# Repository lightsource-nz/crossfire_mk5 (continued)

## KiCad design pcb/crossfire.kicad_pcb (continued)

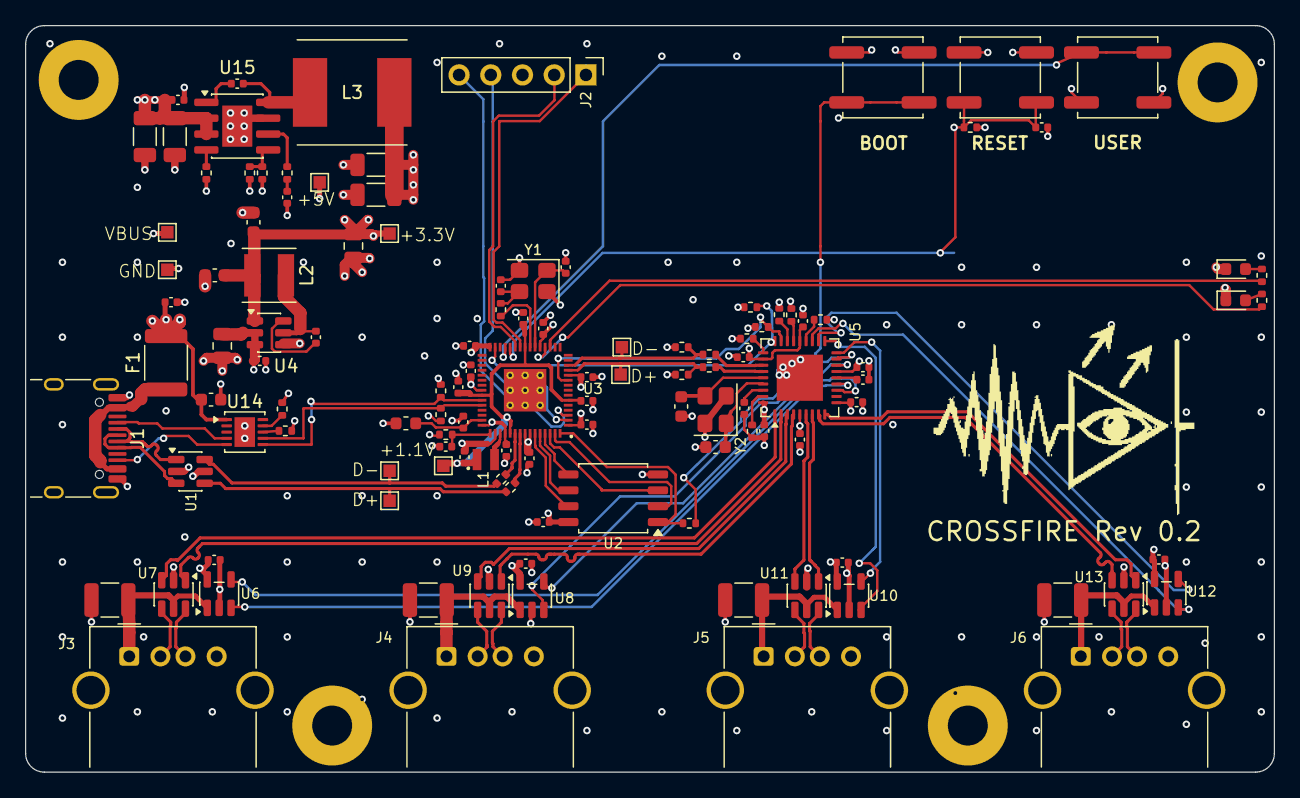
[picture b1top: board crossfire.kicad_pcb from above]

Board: 4 copper layers, 100.0 x 59.8 mm, 124 parts (0 on the bottom side), 92 nets.

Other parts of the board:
G1: crossfire_logo

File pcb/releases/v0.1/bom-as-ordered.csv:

Comment,Designator,Footprint,JLCPCB Part #,Qty,Ext.Price($)
USB-C,J1,USB_C_Receptacle_HRO_TYPE-C-31-M-12_Overhang,C165948,5,0.93
TPS2065C,"U6,U8,U10,U12",SOT-23-5,C353882,22,5.60
RP2350A,U3,rpi_rp2350a_vias,C42411118,5,6.47
330R,"R10,R11",0402,C25104,10,0.01
2.6A,F1,1812,C70127,7,0.43
RESET,"SW1,SW3,SW2",SW_Push_1P1T_NO_CK_KSC6xxJ,C221726,15,9.15
yellow-green,D1,0603,C913102,9,1.06
10k,"R3,R4,R8,R16,R19,R20",0402,C25744,30,0.04
3u3,L1,abracon_aota-b201610s3r3-101-t,C114768,7,0.83
100k,"R12,R24,R25",0402,C25741,15,0.02
4u7,L2,L_4030_Coilcraft_XxL_Sunlord_SWPA,C57269,10,0.66
100R,R9,0402,C25076,5,0.01
12MHz,Y1,Crystal_SMD_3225-4Pin_3.2x2.5mm,C390763,9,0.71
AP63203WU,U4,TSOT-23-6,C780769,5,6.12
W25Q128JVS,U2,SOIC-8,C97521,5,12.90
red,D2,0603,C2286,5,0.04
USBLC6-2SC6,"U1,U7,U9,U11,U13",SOT-23-6,C7519,27,4.85
27R,"R15,R17,R21,R22",0402,C25100,32,0.04
4u7,"C4,C17",0402,C23733,10,0.15
600R,FB1,0603,C85833,20,0.36
10u,"C20,C29",0805,C15850,10,0.43
USB_A,"J3,J4,J5,J6",USB_A_Molex_67643_Horizontal_Overhang,C591765,20,13.71
15p,"C11,C13",0402,C1548,10,0.04
1k,"R7,R23",0402,C11702,10,0.01
100n,"C1,C2,C3,C5,C6,C7,C8,C9,C10,C12,C14,C16,C18,C19,C21,C22,C23,C24,C25,C26,C30,C31,C33,C34,C36,C37,C38,C43,C45",0402,C1525,145,0.51
5k1,"R1,R2",0402,C25905,10,0.02
24MHz,Y2,Crystal_SMD_3225-4Pin_3.2x2.5mm,C70583,9,0.90
12k,R18,0402,C25752,5,0.01
15k,"R13,R14",0402,C25756,10,0.01
22u,"C27,C28",0603,C59461,10,0.31
1u,C15,0402,C29266,25,0.14
18p,"C32,C35",0603,C1647,10,0.12
USB2514B,U5,QFN-36,C16251,5,9.06

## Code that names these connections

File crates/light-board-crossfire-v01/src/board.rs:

//! Board wiring for crossfire revision 0.1: every pin read off the board's own schematic, as
//! recorded in its release specification. Nothing here has been confirmed on hardware yet;
//! the first boards are in production.
//!
//! This lives with the BOARD, not in the port crate or the application: `light-rp2` knows the
//! chip and nothing about what anyone soldered to it, and the application knows neither. This
//! module is the one place that knows which pin carries what, and [`take`] configures every
//! peripheral the board wires up and hands them over once -- the firmware receives owned
//! values, so nothing can reach a peripheral the board did not wire.
//!
//! What the board has, from the processor's side:
//!
//! - the hardware USB pair goes to the USB-C receptacle: the DEVICE role, the console and the
//!   board's entire power supply, and nothing in this module -- the port's shell owns it;
//! - a PIO host pair goes to the hub's upstream port, on [`PIN_HOST_DP`] and [`PIN_HOST_DM`];
//! - the hub is held in reset until the firmware says otherwise, and told when its upstream is
//!   live, on two plain outputs;
//! - two indicators, one button, and the two CC lines of the receptacle on the ADC.
//!
//! The console UART is not constructed here. It is core 1's, built by the firmware's core-1
//! entry on the port's default pair, which is the pair the board wires to the debug header.

use light_core::atomic::{AtomicBool, Ordering};
use light_rp2::adc::Adc;
use light_rp2::gpio::{Input, Output};
use light_rp2::Clocks;

/// The hardware revision this wiring describes, as the board's silkscreen carries it.
pub const REVISION: &str = "0.1";

/// The console, on UART0's default pair, which is also the port's
/// (`light_rp2::shell::UART_TX` / `UART_RX`); brought out on the debug header beside SWD.
pub const PIN_CONSOLE_TX: usize = 0;
pub const PIN_CONSOLE_RX: usize = 1;

/// The hub's active-low reset, with a 10 kΩ pull-down on the board: the hub is held in reset
/// from power-up until this pin is driven high, so a firmware that never touches it has no hub.
pub const PIN_HUB_RESET_N: usize = 7;

/// The PIO USB host pair to the hub's upstream port, 27 Ω in series and 15 kΩ to ground on
/// each line -- the host's pull-downs, so the hub's attach pull-up is seen against them. D+ is
/// the base and D- the next pin up, because the PIO program addresses the pair as a base and
/// an offset.
pub const PIN_HOST_DP: usize = 8;
pub const PIN_HOST_DM: usize = 9;

/// The two indicators, anode to the pin through 330 Ω and cathode to ground: driven high to
/// light, about 4 mA each. The schematic names them LED_1 and LED_2; here they are named by
/// what they look like, since that is what a firmware chooses between.
pub const PIN_LED_RED: usize = 14;
pub const PIN_LED_GREEN: usize = 15;

/// The USER button, to ground, with no pull-up on the board: the pin's own pull-up is what
/// makes it readable, and pressed is low. The other two buttons are not GPIO -- BOOT pulls the
/// flash's chip select and RESET pulls RUN -- so BOOT is read through the port's flash-safe
/// `light_rp2::shell::bootsel`, never as a pin.
pub const PIN_BUTTON: usize = 16;

/// The hub's VBUS_DET input, with a 100 kΩ pull-down on the board: driven high to tell the hub
/// its upstream is live, which is what lets it attach; taken low and high again to make it
/// re-enumerate.
pub const PIN_HUB_VBUS_DET: usize = 18;

/// The receptacle's two CC lines, each terminated with [`CC_RD_OHMS`] to ground at the
/// connector and read here through 10 kΩ and 100 nF: ADC channels 0 and 1. The source's
/// pull-up on whichever line its cable orients to sets the voltage, and that voltage is what
/// the source advertises it can supply.
pub const PIN_CC1_SENSE: usize = 26;
pub const PIN_CC2_SENSE: usize = 27;
/// The termination the board presents on each CC line: the sink's Rd.
pub const CC_RD_OHMS: u32 = 5_100;
/// The ADC's full scale, in millivolts: its reference is the 3.3 V pad supply, through the
/// board's filtered analogue rail.
pub const ADC_FULL_SCALE_MV: u32 = 3_300;

/// The system clock the board is designed for: twenty times its 12 MHz crystal, which gives
/// the PIO host twenty cycles a bit and the flash its fastest legal clock through the divider
/// of 2. The SDK's default is 150 MHz; the firmware's build chooses whether to ask for this.
pub const DESIGN_SYS_HZ: u32 = 240_000_000;

pub struct Peripherals {
        /// Off until lit.
        pub led_red: Output,
        pub led_green: Output,
        /// Pulled up; pressed is low.
        pub button: Input,
        /// Low: the hub is held in reset, as the board's pull-down leaves it from power-up.
        pub hub_reset_n: Output,
        /// Low: the hub has not been told its upstream is live.
        pub hub_vbus_det: Output,
        /// One-shot reads, 12 bits over [`ADC_FULL_SCALE_MV`].
        pub cc1: Adc,
        pub cc2: Adc,
}

static TAKEN: AtomicBool = AtomicBool::new(false);

/// Configure and hand over the board's peripherals. Once.
///
/// Nothing wired today needs a clock rate; the host pair's PIO will, and takes it from here.
pub fn take(clocks: &Clocks) -> Option<Peripherals> {
        if TAKEN.swap(true, Ordering::AcqRel) {
                return None;
        }
        let _ = clocks;
        //   the hub stays exactly where the board's pull-downs put it at power-up -- in reset,
        // with no upstream -- until a firmware decides otherwise: an output constructed low
        // changes nothing on the wire
        Some(Peripherals {
                led_red: Output::new(PIN_LED_RED, false),
                led_green: Output::new(PIN_LED_GREEN, false),
                button: Input::new_pull_up(PIN_BUTTON),
                hub_reset_n: Output::new(PIN_HUB_RESET_N, false),
                hub_vbus_det: Output::new(PIN_HUB_VBUS_DET, false),
                cc1: Adc::new(PIN_CC1_SENSE),
                cc2: Adc::new(PIN_CC2_SENSE),
        })
}
